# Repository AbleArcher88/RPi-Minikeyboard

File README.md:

# RPi-Minikeyboard
Handheld minerature keyboard for Raspberry Pi 4 (and hopefully later)

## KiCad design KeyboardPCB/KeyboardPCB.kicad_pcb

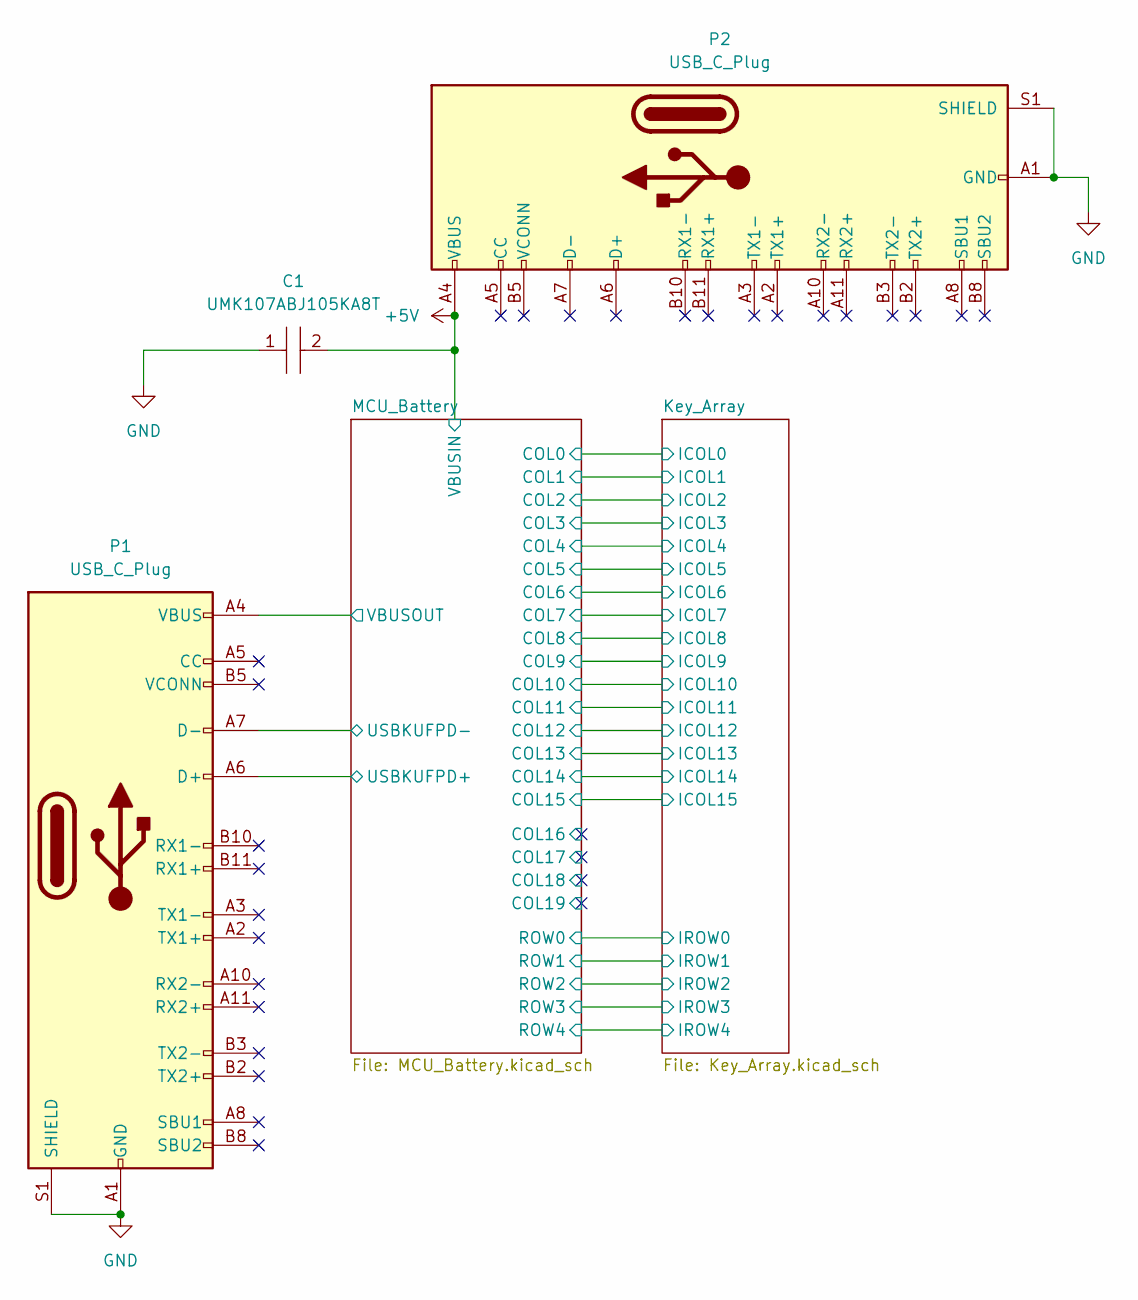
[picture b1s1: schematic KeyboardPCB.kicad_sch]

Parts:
C1: UMK107ABJ105KA8T; CAPC1608X95N; Mouser Part Number 963-UMK107ABJ105KA8T
P1, P2: USB_C_Plug; USB_C_Receptacle_Amphenol_12401548E4-2A

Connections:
+5V: C1.2, P2.A4 (VBUS), P2.A9 (VBUS), P2.B4 (VBUS), P2.B9 (VBUS); also elsewhere on the board
/MCU_Battery/USBKUFPD+: P1.A6 (D+); also elsewhere on the board
/MCU_Battery/USBKUFPD-: P1.A7 (D-); also elsewhere on the board
/MCU_Battery/VBUSOUT: P1.A4 (VBUS), P1.A9 (VBUS), P1.B4 (VBUS), P1.B9 (VBUS); also elsewhere on the board
GND: C1.1, P1.A1 (GND), P1.A12 (GND), P1.B1 (GND), P1.B12 (GND), P1.S1 (SHIELD), P2.A1 (GND), P2.A12 (GND), P2.B1 (GND), P2.B12 (GND), P2.S1 (SHIELD); also elsewhere on the board

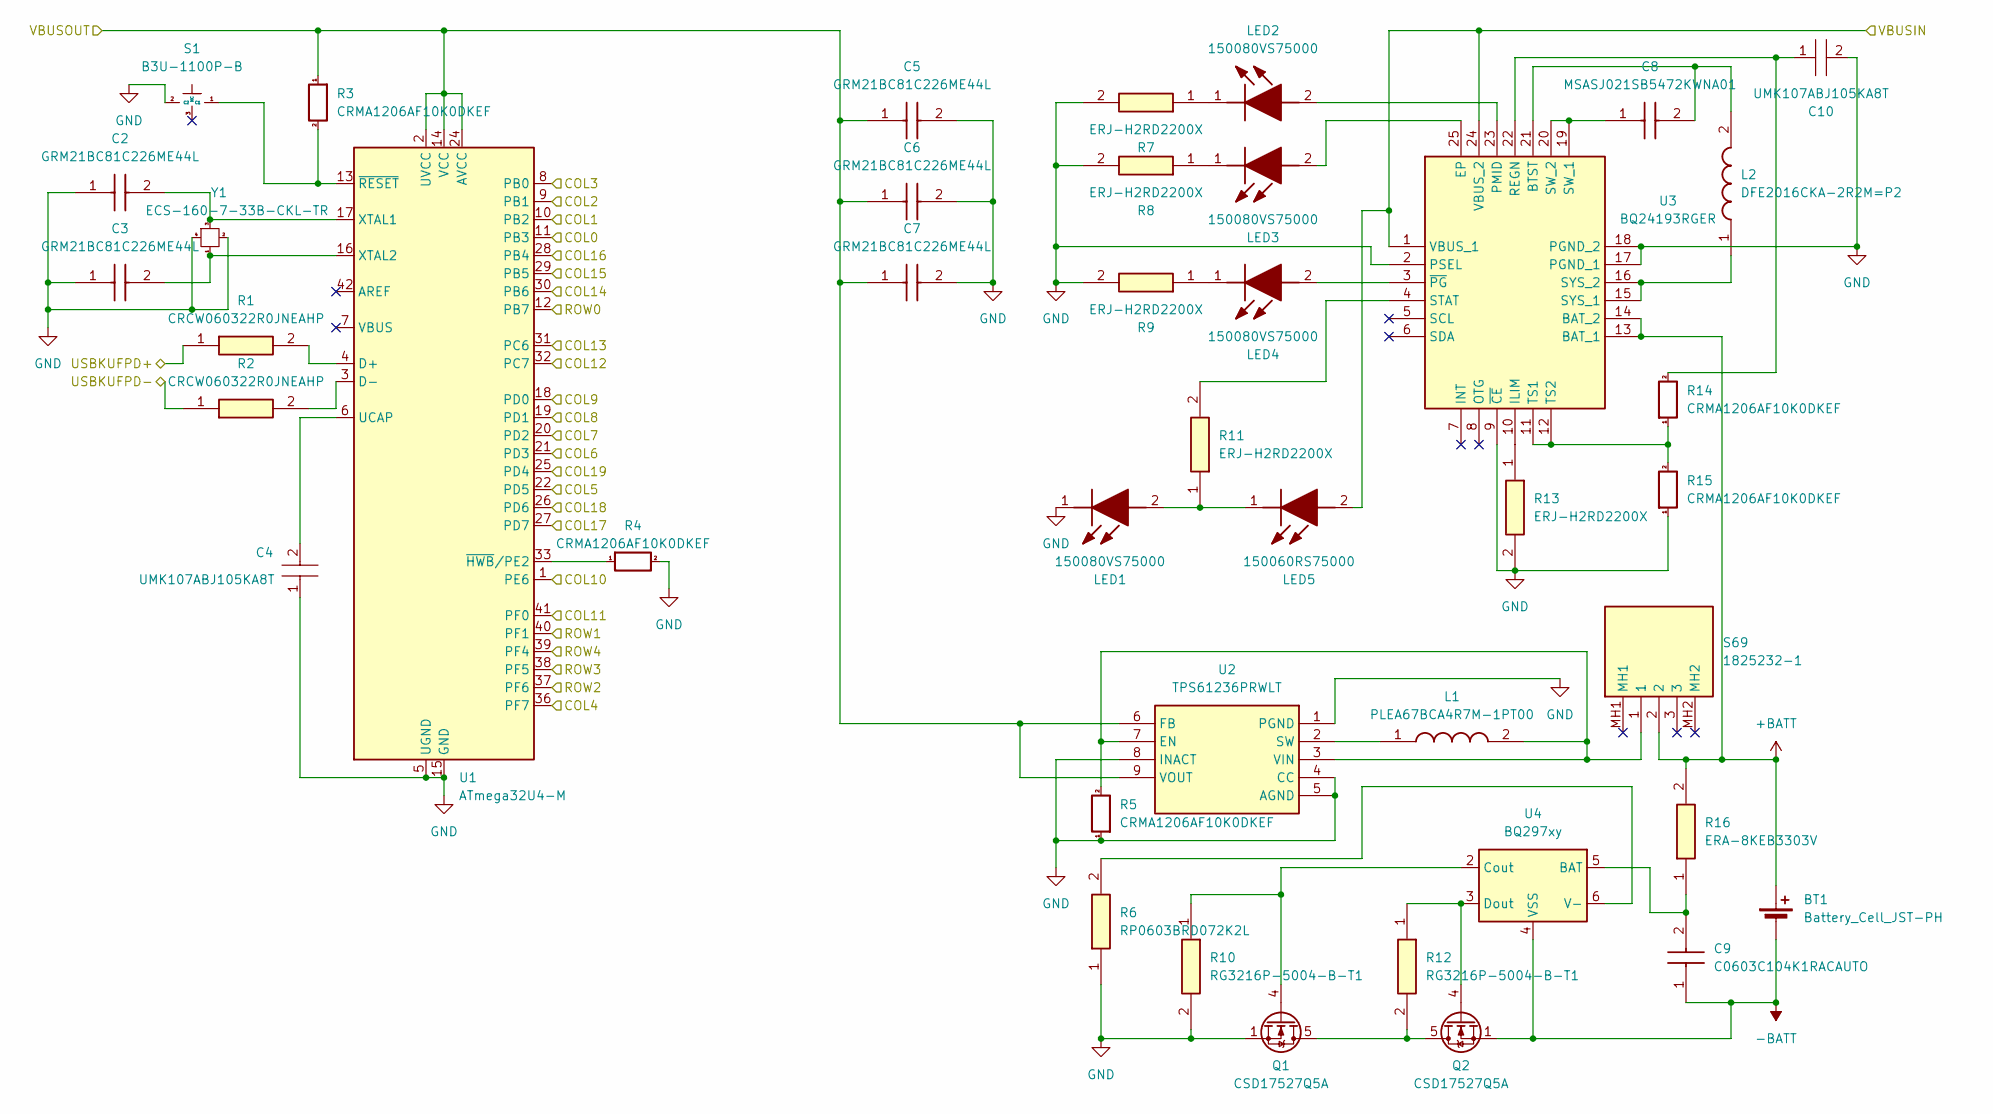
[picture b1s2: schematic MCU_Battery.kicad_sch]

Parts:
BT1: Battery_Cell_JST-PH; JST_PH_B2B-PH-K_1x02_P2.00mm_Vertical
C2, C3, C5, C6, C7: GRM21BC81C226ME44L; CAPC2012X145N; Manufacturer_Part_Number GRM21BC81C226ME44L; Mouser Part Number 81-GRM21BC81C226ME4L
C4, C10: UMK107ABJ105KA8T; CAPC1608X95N; Mouser Part Number 963-UMK107ABJ105KA8T
C8: MSASJ021SB5472KWNA01; CAPC0201X14N; Manufacturer_Part_Number MSASJ021SB5472KWNA01; Mouser Part Number 963-MSASJ021SB5472KW
C9: C0603C104K1RACAUTO; CAPC1608X95N; Manufacturer_Part_Number C0603C104K1RACAUTO; Mouser Part Number 80-C0603C104K1RAUTO
L1: PLEA67BCA4R7M-1PT00; PLEA67BCA4R7M1PT00; Manufacturer_Part_Number PLEA67BCA4R7M-1PT00; Mouser Part Number 810-PLEA67BCA4R7M1PT
L2: DFE2016CKA-2R2M=P2; DFE2016CKA1R0MP2; Manufacturer_Part_Number DFE2016CKA-2R2M=P2; Mouser Part Number 81-DFE2016CKA2R2M=P2
LED1, LED2, LED3, LED4: 150080VS75000; LEDC2012X80N; Manufacturer_Part_Number 150080VS75000; Mouser Part Number 710-150080VS75000
LED5: 150060RS75000; LEDC1608X80N; Manufacturer_Part_Number 150060RS75000; Mouser Part Number 710-150060RS75000
Q1, Q2: CSD17527Q5A; TDSON-8-1
R1, R2: CRCW060322R0JNEAHP; RESC1608X50N; Manufacturer_Part_Number CRCW060322R0JNEAHP; Mouser Part Number 71-CRCW060322R0JNEAH
R3, R4, R5, R14, R15: CRMA1206AF10K0DKEF; RESC3216X74N; Mouser Part Number 71-CRMA1206AF10K0DKF
R6: RP0603BRD072K2L; RESC1608X55N; Manufacturer_Part_Number RP0603BRD072K2L; Mouser Part Number 603-RP0603BRD072K2L
R7, R8, R9, R11, R13: ERJ-H2RD2200X; H2C_H2R; Manufacturer_Part_Number ERJ-H2RD2200X; Mouser Part Number 667-ERJ-H2RD2200X
R10, R12: RG3216P-5004-B-T1; RESC3216X50N; Manufacturer_Part_Number RG3216P-5004-B-T1; Mouser Part Number 754-RG3216P-5004B-T1
R16: ERA-8KEB3303V; ERA8KEB1004V; Manufacturer_Part_Number ERA-8KEB3303V; Mouser Part Number 667-ERA-8KEB3303V
S1: B3U-1100P-B; B3U1100PB; Manufacturer_Part_Number B3U-1100P-B; Mouser Part Number 653-B3U-1100P-B
S69: 1825232-1; 18252321; Manufacturer_Part_Number 1825232-1; Mouser Part Number 655-1825232-1
U1: ATmega32U4-M; QFN-44-1EP_7x7mm_P0.5mm_EP5.2x5.2mm
U2: TPS61236PRWLT; TPS61235PRWLT; Manufacturer_Part_Number TPS61236PRWLT; Mouser Part Number 595-TPS61236PRWLT
U3: BQ24193RGER; QFN50P400X400X100-25N-D; Manufacturer_Part_Number BQ24193RGER; Mouser Part Number 595-BQ24193RGER
U4: BQ297xy; WSON-6_1.5x1.5mm_P0.5mm
Y1: ECS-160-7-33B-CKL-TR; ECS160733BCKLTR; Manufacturer_Part_Number ECS-160-7-33B-CKL-TR

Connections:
+5V: LED5.2 (A), U3.1 (VBUS_1), U3.24 (VBUS_2); also elsewhere on the board
+BATT: BT1.1 (+), R16.2, S69.2, U3.13 (BAT_1), U3.14 (BAT_2)
-BATT: BT1.2 (-), C9.1, Q2.1 (S), Q2.2 (S), Q2.3 (S), U4.4 (VSS)
/Key_Array/ICOL0: U1.11 (PB3); also elsewhere on the board
/Key_Array/ICOL1: U1.10 (PB2); also elsewhere on the board
/Key_Array/ICOL2: U1.9 (PB1); also elsewhere on the board
/Key_Array/ICOL3: U1.8 (PB0); also elsewhere on the board
/Key_Array/ICOL4: U1.36 (PF7); also elsewhere on the board
/Key_Array/ICOL5: U1.22 (PD5); also elsewhere on the board
/Key_Array/ICOL6: U1.21 (PD3); also elsewhere on the board
/Key_Array/ICOL7: U1.20 (PD2); also elsewhere on the board
/Key_Array/ICOL8: U1.19 (PD1); also elsewhere on the board
/Key_Array/ICOL9: U1.18 (PD0); also elsewhere on the board
/Key_Array/ICOL10: U1.1 (PE6); also elsewhere on the board
/Key_Array/ICOL11: U1.41 (PF0); also elsewhere on the board
/Key_Array/ICOL12: U1.32 (PC7); also elsewhere on the board
/Key_Array/ICOL13: U1.31 (PC6); also elsewhere on the board
/Key_Array/ICOL14: U1.30 (PB6)
/Key_Array/ICOL15: U1.29 (PB5)
/Key_Array/IROW0: U1.12 (PB7); also elsewhere on the board
/Key_Array/IROW1: U1.40 (PF1); also elsewhere on the board
/Key_Array/IROW2: U1.37 (PF6); also elsewhere on the board
/Key_Array/IROW3: U1.38 (PF5); also elsewhere on the board
/Key_Array/IROW4: U1.39 (PF4); also elsewhere on the board
/MCU_Battery/COL16: U1.28 (PB4)
/MCU_Battery/COL17: U1.27 (PD7)
/MCU_Battery/COL18: U1.26 (PD6)
/MCU_Battery/COL19: U1.25 (PD4)
/MCU_Battery/USBKUFPD+: R1.1; also elsewhere on the board
/MCU_Battery/USBKUFPD-: R2.1; also elsewhere on the board
/MCU_Battery/VBUSOUT: C5.1, C6.1, C7.1, R3.1, U1.2 (UVCC), U1.14 (VCC), U1.24 (AVCC), U1.34 (VCC), U1.44 (AVCC), U2.6 (FB), U2.9 (VOUT); also elsewhere on the board
GND: C2.1, C3.1, C4.1, C5.2, C6.2, C7.2, C10.2, LED1.1 (K), Q1.1 (S), Q1.2 (S), Q1.3 (S), R4.2, R5.1, R6.1, R7.2, R8.2, R9.2, R10.2, R13.2, R15.1, S1.2 (C2), U1.5 (UGND), U1.15 (GND), U1.23 (GND), U1.35 (GND), U1.43 (GND), U1.45 (GND), U2.1 (PGND), U2.4 (CC), U2.5 (AGND), U2.8 (INACT), U3.2 (PSEL), U3.9 (~CE), U3.17 (PGND_1), U3.18 (PGND_2), Y1.2, Y1.4; also elsewhere on the board
unnamed: LED1.2 (A), LED5.1 (K), R11.1
unnamed: LED2.2 (A), U3.23 (PMID)
unnamed: LED2.1 (K), R7.1
unnamed: LED3.2 (A), U3.25 (EP)
unnamed: LED3.1 (K), R8.1
unnamed: LED4.2 (A), U3.3 (~PG)
unnamed: LED4.1 (K), R9.1
unnamed: Q1.5 (D), Q2.5 (D), R12.2
unnamed: Q1.4 (G), R10.1, U4.2 (Cout)
unnamed: Q2.4 (G), R12.1, U4.3 (Dout)
unnamed: R3.2, S1.1 (C1), U1.13 (~RESET)
unnamed: R1.2, U1.4 (D+)
unnamed: R2.2, U1.3 (D-)
unnamed: C4.2, U1.6 (UCAP)
unnamed: C2.2, U1.17 (XTAL1), Y1.3
unnamed: C3.2, U1.16 (XTAL2), Y1.1
unnamed: R4.1, U1.33 (~HWB/PE2)
unnamed: L1.2, R5.2, S69.1, U2.3 (VIN), U2.7 (EN)
unnamed: L1.1, U2.2 (SW)
unnamed: C8.2, L2.2, U3.21 (BTST)
unnamed: R13.1, U3.10 (ILIM)
unnamed: C10.1, R14.2, U3.22 (REGN)
unnamed: R11.2, U3.4 (STAT)
unnamed: C8.1, U3.19 (SW_1), U3.20 (SW_2)
unnamed: L2.1, U3.15 (SYS_1), U3.16 (SYS_2)
unnamed: R14.1, R15.2, U3.11 (TS1), U3.12 (TS2)
unnamed: C9.2, R16.1, U4.5 (BAT)
unnamed: R6.2, U4.6 (V-)

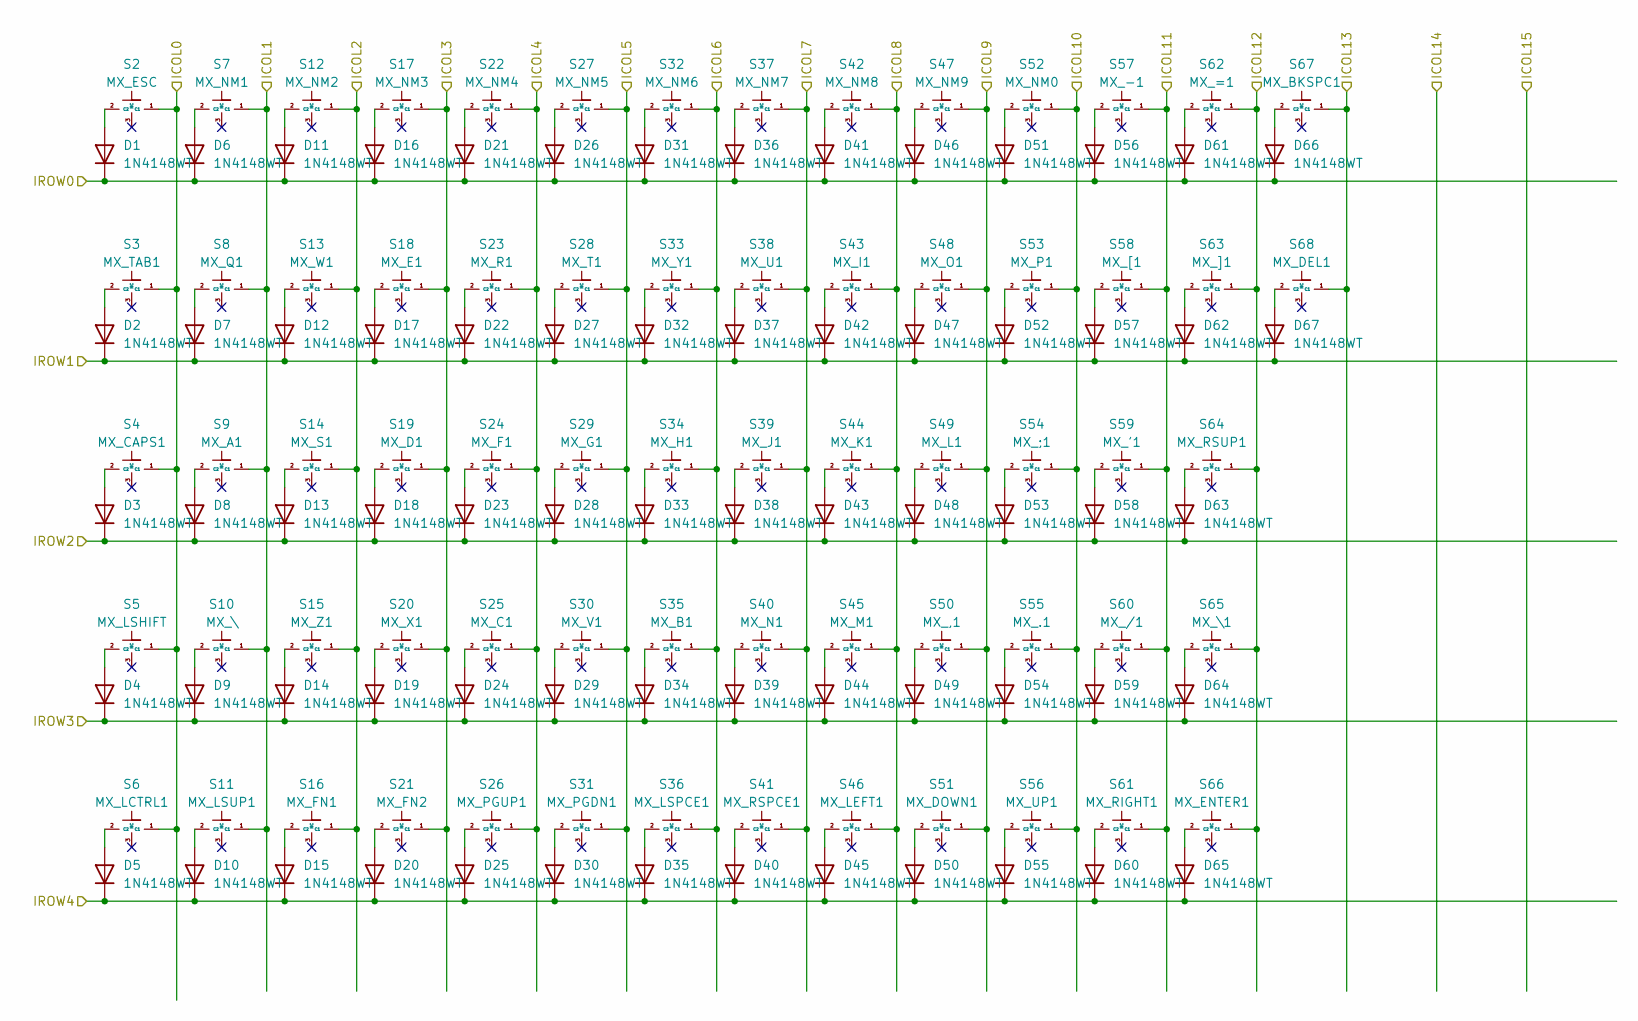
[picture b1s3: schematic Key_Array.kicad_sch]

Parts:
D1, D2, D3, D4, D5, D6, D7, D8, D9, D10, D11, D12, D13, D14, D15, D16, D17, D18, D19, D20, D21, D22, D23, D24, D25, D26, D27, D28, D29, D30, D31, D32, D33, D34, D35, D36, D37, D38, D39, D40, D41, D42, D43, D44, D45, D46, D47, D48, D49, D50, D51, D52, D53, D54, D55, D56, D57, D58, D59, D60, D61, D62, D63, D64, D65, D66, D67: 1N4148WT; D_SOD-523
S2: MX_ESC; B3U1100PB; Manufacturer_Part_Number B3U-1100P-B; Mouser Part Number 653-B3U-1100P-B
S3: MX_TAB1; B3U1100PB; Manufacturer_Part_Number B3U-1100P-B; Mouser Part Number 653-B3U-1100P-B
S4: MX_CAPS1; B3U1100PB; Manufacturer_Part_Number B3U-1100P-B; Mouser Part Number 653-B3U-1100P-B
S5: MX_LSHIFT; B3U1100PB; Manufacturer_Part_Number B3U-1100P-B; Mouser Part Number 653-B3U-1100P-B
S6: MX_LCTRL1; B3U1100PB; Manufacturer_Part_Number B3U-1100P-B; Mouser Part Number 653-B3U-1100P-B
S7: MX_NM1; B3U1100PB; Manufacturer_Part_Number B3U-1100P-B; Mouser Part Number 653-B3U-1100P-B
S8: MX_Q1; B3U1100PB; Manufacturer_Part_Number B3U-1100P-B; Mouser Part Number 653-B3U-1100P-B
S9: MX_A1; B3U1100PB; Manufacturer_Part_Number B3U-1100P-B; Mouser Part Number 653-B3U-1100P-B
S10: MX_\; B3U1100PB; Manufacturer_Part_Number B3U-1100P-B; Mouser Part Number 653-B3U-1100P-B
S11: MX_LSUP1; B3U1100PB; Manufacturer_Part_Number B3U-1100P-B; Mouser Part Number 653-B3U-1100P-B
S12: MX_NM2; B3U1100PB; Manufacturer_Part_Number B3U-1100P-B; Mouser Part Number 653-B3U-1100P-B
S13: MX_W1; B3U1100PB; Manufacturer_Part_Number B3U-1100P-B; Mouser Part Number 653-B3U-1100P-B
S14: MX_S1; B3U1100PB; Manufacturer_Part_Number B3U-1100P-B; Mouser Part Number 653-B3U-1100P-B
S15: MX_Z1; B3U1100PB; Manufacturer_Part_Number B3U-1100P-B; Mouser Part Number 653-B3U-1100P-B
S16: MX_FN1; B3U1100PB; Manufacturer_Part_Number B3U-1100P-B; Mouser Part Number 653-B3U-1100P-B
S17: MX_NM3; B3U1100PB; Manufacturer_Part_Number B3U-1100P-B; Mouser Part Number 653-B3U-1100P-B
S18: MX_E1; B3U1100PB; Manufacturer_Part_Number B3U-1100P-B; Mouser Part Number 653-B3U-1100P-B
S19: MX_D1; B3U1100PB; Manufacturer_Part_Number B3U-1100P-B; Mouser Part Number 653-B3U-1100P-B
S20: MX_X1; B3U1100PB; Manufacturer_Part_Number B3U-1100P-B; Mouser Part Number 653-B3U-1100P-B
S21: MX_FN2; B3U1100PB; Manufacturer_Part_Number B3U-1100P-B; Mouser Part Number 653-B3U-1100P-B
S22: MX_NM4; B3U1100PB; Manufacturer_Part_Number B3U-1100P-B; Mouser Part Number 653-B3U-1100P-B
S23: MX_R1; B3U1100PB; Manufacturer_Part_Number B3U-1100P-B; Mouser Part Number 653-B3U-1100P-B
S24: MX_F1; B3U1100PB; Manufacturer_Part_Number B3U-1100P-B; Mouser Part Number 653-B3U-1100P-B
S25: MX_C1; B3U1100PB; Manufacturer_Part_Number B3U-1100P-B; Mouser Part Number 653-B3U-1100P-B
S26: MX_PGUP1; B3U1100PB; Manufacturer_Part_Number B3U-1100P-B; Mouser Part Number 653-B3U-1100P-B
S27: MX_NM5; B3U1100PB; Manufacturer_Part_Number B3U-1100P-B; Mouser Part Number 653-B3U-1100P-B
S28: MX_T1; B3U1100PB; Manufacturer_Part_Number B3U-1100P-B; Mouser Part Number 653-B3U-1100P-B
S29: MX_G1; B3U1100PB; Manufacturer_Part_Number B3U-1100P-B; Mouser Part Number 653-B3U-1100P-B
S30: MX_V1; B3U1100PB; Manufacturer_Part_Number B3U-1100P-B; Mouser Part Number 653-B3U-1100P-B
S31: MX_PGDN1; B3U1100PB; Manufacturer_Part_Number B3U-1100P-B; Mouser Part Number 653-B3U-1100P-B
S32: MX_NM6; B3U1100PB; Manufacturer_Part_Number B3U-1100P-B; Mouser Part Number 653-B3U-1100P-B
S33: MX_Y1; B3U1100PB; Manufacturer_Part_Number B3U-1100P-B; Mouser Part Number 653-B3U-1100P-B
S34: MX_H1; B3U1100PB; Manufacturer_Part_Number B3U-1100P-B; Mouser Part Number 653-B3U-1100P-B
S35: MX_B1; B3U1100PB; Manufacturer_Part_Number B3U-1100P-B; Mouser Part Number 653-B3U-1100P-B
S36: MX_LSPCE1; B3U1100PB; Manufacturer_Part_Number B3U-1100P-B; Mouser Part Number 653-B3U-1100P-B
S37: MX_NM7; B3U1100PB; Manufacturer_Part_Number B3U-1100P-B; Mouser Part Number 653-B3U-1100P-B
S38: MX_U1; B3U1100PB; Manufacturer_Part_Number B3U-1100P-B; Mouser Part Number 653-B3U-1100P-B
S39: MX_J1; B3U1100PB; Manufacturer_Part_Number B3U-1100P-B; Mouser Part Number 653-B3U-1100P-B
S40: MX_N1; B3U1100PB; Manufacturer_Part_Number B3U-1100P-B; Mouser Part Number 653-B3U-1100P-B
S41: MX_RSPCE1; B3U1100PB; Manufacturer_Part_Number B3U-1100P-B; Mouser Part Number 653-B3U-1100P-B
S42: MX_NM8; B3U1100PB; Manufacturer_Part_Number B3U-1100P-B; Mouser Part Number 653-B3U-1100P-B
S43: MX_I1; B3U1100PB; Manufacturer_Part_Number B3U-1100P-B; Mouser Part Number 653-B3U-1100P-B
S44: MX_K1; B3U1100PB; Manufacturer_Part_Number B3U-1100P-B; Mouser Part Number 653-B3U-1100P-B
S45: MX_M1; B3U1100PB; Manufacturer_Part_Number B3U-1100P-B; Mouser Part Number 653-B3U-1100P-B
S46: MX_LEFT1; B3U1100PB; Manufacturer_Part_Number B3U-1100P-B; Mouser Part Number 653-B3U-1100P-B
S47: MX_NM9; B3U1100PB; Manufacturer_Part_Number B3U-1100P-B; Mouser Part Number 653-B3U-1100P-B
S48: MX_O1; B3U1100PB; Manufacturer_Part_Number B3U-1100P-B; Mouser Part Number 653-B3U-1100P-B
S49: MX_L1; B3U1100PB; Manufacturer_Part_Number B3U-1100P-B; Mouser Part Number 653-B3U-1100P-B
S50: MX_,1; B3U1100PB; Manufacturer_Part_Number B3U-1100P-B; Mouser Part Number 653-B3U-1100P-B
S51: MX_DOWN1; B3U1100PB; Manufacturer_Part_Number B3U-1100P-B; Mouser Part Number 653-B3U-1100P-B
S52: MX_NM0; B3U1100PB; Manufacturer_Part_Number B3U-1100P-B; Mouser Part Number 653-B3U-1100P-B
S53: MX_P1; B3U1100PB; Manufacturer_Part_Number B3U-1100P-B; Mouser Part Number 653-B3U-1100P-B
S54: MX_;1; B3U1100PB; Manufacturer_Part_Number B3U-1100P-B; Mouser Part Number 653-B3U-1100P-B
S55: MX_.1; B3U1100PB; Manufacturer_Part_Number B3U-1100P-B; Mouser Part Number 653-B3U-1100P-B
S56: MX_UP1; B3U1100PB; Manufacturer_Part_Number B3U-1100P-B; Mouser Part Number 653-B3U-1100P-B
S57: MX_-1; B3U1100PB; Manufacturer_Part_Number B3U-1100P-B; Mouser Part Number 653-B3U-1100P-B
S58: MX_[1; B3U1100PB; Manufacturer_Part_Number B3U-1100P-B; Mouser Part Number 653-B3U-1100P-B
S59: MX_'1; B3U1100PB; Manufacturer_Part_Number B3U-1100P-B; Mouser Part Number 653-B3U-1100P-B
S60: MX_/1; B3U1100PB; Manufacturer_Part_Number B3U-1100P-B; Mouser Part Number 653-B3U-1100P-B
S61: MX_RIGHT1; B3U1100PB; Manufacturer_Part_Number B3U-1100P-B; Mouser Part Number 653-B3U-1100P-B
S62: MX_=1; B3U1100PB; Manufacturer_Part_Number B3U-1100P-B; Mouser Part Number 653-B3U-1100P-B
S63: MX_]1; B3U1100PB; Manufacturer_Part_Number B3U-1100P-B; Mouser Part Number 653-B3U-1100P-B
S64: MX_RSUP1; B3U1100PB; Manufacturer_Part_Number B3U-1100P-B; Mouser Part Number 653-B3U-1100P-B
S65: MX_\1; B3U1100PB; Manufacturer_Part_Number B3U-1100P-B; Mouser Part Number 653-B3U-1100P-B
S66: MX_ENTER1; B3U1100PB; Manufacturer_Part_Number B3U-1100P-B; Mouser Part Number 653-B3U-1100P-B
S67: MX_BKSPC1; B3U1100PB; Manufacturer_Part_Number B3U-1100P-B; Mouser Part Number 653-B3U-1100P-B
S68: MX_DEL1; B3U1100PB; Manufacturer_Part_Number B3U-1100P-B; Mouser Part Number 653-B3U-1100P-B

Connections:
/Key_Array/ICOL0: S2.1 (C1), S3.1 (C1), S4.1 (C1), S5.1 (C1), S6.1 (C1); also elsewhere on the board
/Key_Array/ICOL1: S7.1 (C1), S8.1 (C1), S9.1 (C1), S10.1 (C1), S11.1 (C1); also elsewhere on the board
/Key_Array/ICOL2: S12.1 (C1), S13.1 (C1), S14.1 (C1), S15.1 (C1), S16.1 (C1); also elsewhere on the board
/Key_Array/ICOL3: S17.1 (C1), S18.1 (C1), S19.1 (C1), S20.1 (C1), S21.1 (C1); also elsewhere on the board
/Key_Array/ICOL4: S22.1 (C1), S23.1 (C1), S24.1 (C1), S25.1 (C1), S26.1 (C1); also elsewhere on the board
/Key_Array/ICOL5: S27.1 (C1), S28.1 (C1), S29.1 (C1), S30.1 (C1), S31.1 (C1); also elsewhere on the board
/Key_Array/ICOL6: S32.1 (C1), S33.1 (C1), S34.1 (C1), S35.1 (C1), S36.1 (C1); also elsewhere on the board
/Key_Array/ICOL7: S37.1 (C1), S38.1 (C1), S39.1 (C1), S40.1 (C1), S41.1 (C1); also elsewhere on the board
/Key_Array/ICOL8: S42.1 (C1), S43.1 (C1), S44.1 (C1), S45.1 (C1), S46.1 (C1); also elsewhere on the board
/Key_Array/ICOL9: S47.1 (C1), S48.1 (C1), S49.1 (C1), S50.1 (C1), S51.1 (C1); also elsewhere on the board
/Key_Array/ICOL10: S52.1 (C1), S53.1 (C1), S54.1 (C1), S55.1 (C1), S56.1 (C1); also elsewhere on the board
/Key_Array/ICOL11: S57.1 (C1), S58.1 (C1), S59.1 (C1), S60.1 (C1), S61.1 (C1); also elsewhere on the board
/Key_Array/ICOL12: S62.1 (C1), S63.1 (C1), S64.1 (C1), S65.1 (C1), S66.1 (C1); also elsewhere on the board
/Key_Array/ICOL13: S67.1 (C1), S68.1 (C1); also elsewhere on the board
/Key_Array/IROW0: D1.1 (K), D6.1 (K), D11.1 (K), D16.1 (K), D21.1 (K), D26.1 (K), D31.1 (K), D36.1 (K), D41.1 (K), D46.1 (K), D51.1 (K), D56.1 (K), D61.1 (K), D66.1 (K); also elsewhere on the board
/Key_Array/IROW1: D2.1 (K), D7.1 (K), D12.1 (K), D17.1 (K), D22.1 (K), D27.1 (K), D32.1 (K), D37.1 (K), D42.1 (K), D47.1 (K), D52.1 (K), D57.1 (K), D62.1 (K), D67.1 (K); also elsewhere on the board
/Key_Array/IROW2: D3.1 (K), D8.1 (K), D13.1 (K), D18.1 (K), D23.1 (K), D28.1 (K), D33.1 (K), D38.1 (K), D43.1 (K), D48.1 (K), D53.1 (K), D58.1 (K), D63.1 (K); also elsewhere on the board
/Key_Array/IROW3: D4.1 (K), D9.1 (K), D14.1 (K), D19.1 (K), D24.1 (K), D29.1 (K), D34.1 (K), D39.1 (K), D44.1 (K), D49.1 (K), D54.1 (K), D59.1 (K), D64.1 (K); also elsewhere on the board
/Key_Array/IROW4: D5.1 (K), D10.1 (K), D15.1 (K), D20.1 (K), D25.1 (K), D30.1 (K), D35.1 (K), D40.1 (K), D45.1 (K), D50.1 (K), D55.1 (K), D60.1 (K), D65.1 (K); also elsewhere on the board
unnamed: D1.2 (A), S2.2 (C2)
unnamed: D2.2 (A), S3.2 (C2)
unnamed: D3.2 (A), S4.2 (C2)
unnamed: D4.2 (A), S5.2 (C2)
unnamed: D5.2 (A), S6.2 (C2)
unnamed: D6.2 (A), S7.2 (C2)
unnamed: D7.2 (A), S8.2 (C2)
unnamed: D8.2 (A), S9.2 (C2)
unnamed: D9.2 (A), S10.2 (C2)
unnamed: D10.2 (A), S11.2 (C2)
unnamed: D11.2 (A), S12.2 (C2)
unnamed: D12.2 (A), S13.2 (C2)
unnamed: D13.2 (A), S14.2 (C2)
unnamed: D14.2 (A), S15.2 (C2)
unnamed: D15.2 (A), S16.2 (C2)
unnamed: D16.2 (A), S17.2 (C2)
unnamed: D17.2 (A), S18.2 (C2)
unnamed: D18.2 (A), S19.2 (C2)
unnamed: D19.2 (A), S20.2 (C2)
unnamed: D20.2 (A), S21.2 (C2)
unnamed: D21.2 (A), S22.2 (C2)
unnamed: D22.2 (A), S23.2 (C2)
unnamed: D23.2 (A), S24.2 (C2)
unnamed: D24.2 (A), S25.2 (C2)
unnamed: D25.2 (A), S26.2 (C2)
unnamed: D26.2 (A), S27.2 (C2)
unnamed: D27.2 (A), S28.2 (C2)
unnamed: D28.2 (A), S29.2 (C2)
unnamed: D29.2 (A), S30.2 (C2)
unnamed: D30.2 (A), S31.2 (C2)
unnamed: D31.2 (A), S32.2 (C2)
unnamed: D32.2 (A), S33.2 (C2)
unnamed: D33.2 (A), S34.2 (C2)
unnamed: D34.2 (A), S35.2 (C2)
unnamed: D35.2 (A), S36.2 (C2)
unnamed: D36.2 (A), S37.2 (C2)
unnamed: D37.2 (A), S38.2 (C2)
unnamed: D38.2 (A), S39.2 (C2)
unnamed: D39.2 (A), S40.2 (C2)
unnamed: D40.2 (A), S41.2 (C2)
unnamed: D41.2 (A), S42.2 (C2)
unnamed: D42.2 (A), S43.2 (C2)
unnamed: D43.2 (A), S44.2 (C2)
unnamed: D44.2 (A), S45.2 (C2)
unnamed: D45.2 (A), S46.2 (C2)
unnamed: D46.2 (A), S47.2 (C2)
unnamed: D47.2 (A), S48.2 (C2)
unnamed: D48.2 (A), S49.2 (C2)
unnamed: D49.2 (A), S50.2 (C2)
unnamed: D50.2 (A), S51.2 (C2)
unnamed: D51.2 (A), S52.2 (C2)
unnamed: D52.2 (A), S53.2 (C2)
unnamed: D53.2 (A), S54.2 (C2)
unnamed: D54.2 (A), S55.2 (C2)
unnamed: D55.2 (A), S56.2 (C2)
unnamed: D56.2 (A), S57.2 (C2)
unnamed: D57.2 (A), S58.2 (C2)
unnamed: D58.2 (A), S59.2 (C2)
unnamed: D59.2 (A), S60.2 (C2)
unnamed: D60.2 (A), S61.2 (C2)
unnamed: D61.2 (A), S62.2 (C2)
unnamed: D62.2 (A), S63.2 (C2)
unnamed: D63.2 (A), S64.2 (C2)
unnamed: D64.2 (A), S65.2 (C2)
unnamed: D65.2 (A), S66.2 (C2)
unnamed: D66.2 (A), S67.2 (C2)
unnamed: D67.2 (A), S68.2 (C2)

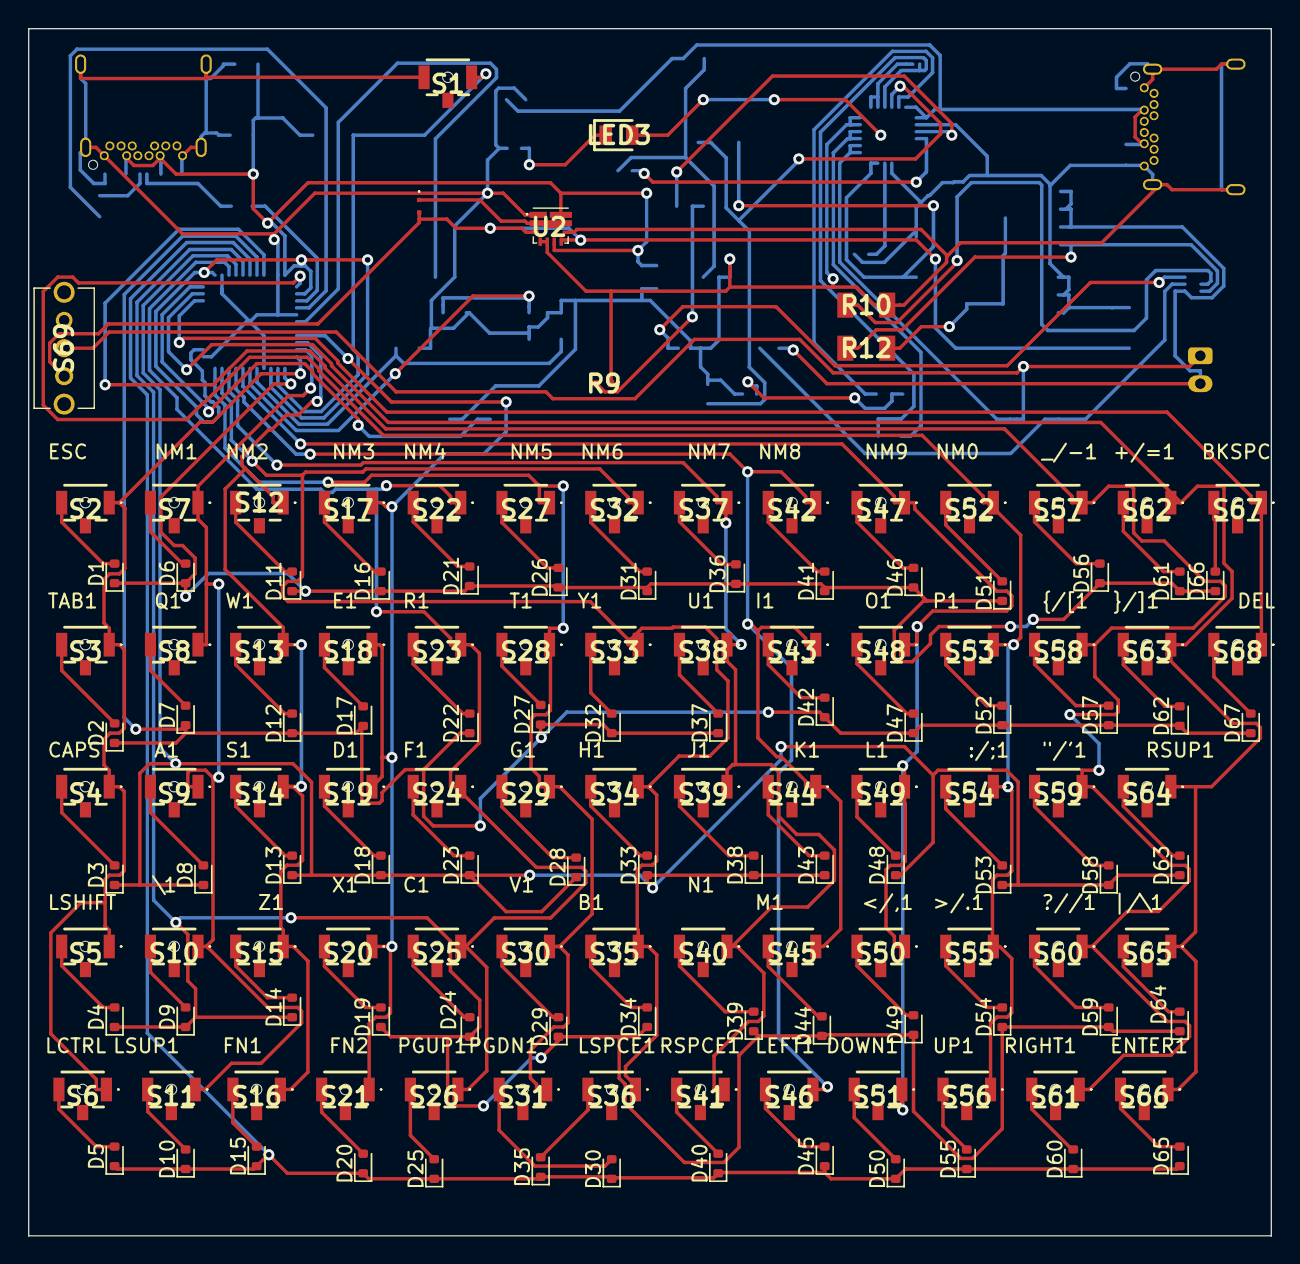
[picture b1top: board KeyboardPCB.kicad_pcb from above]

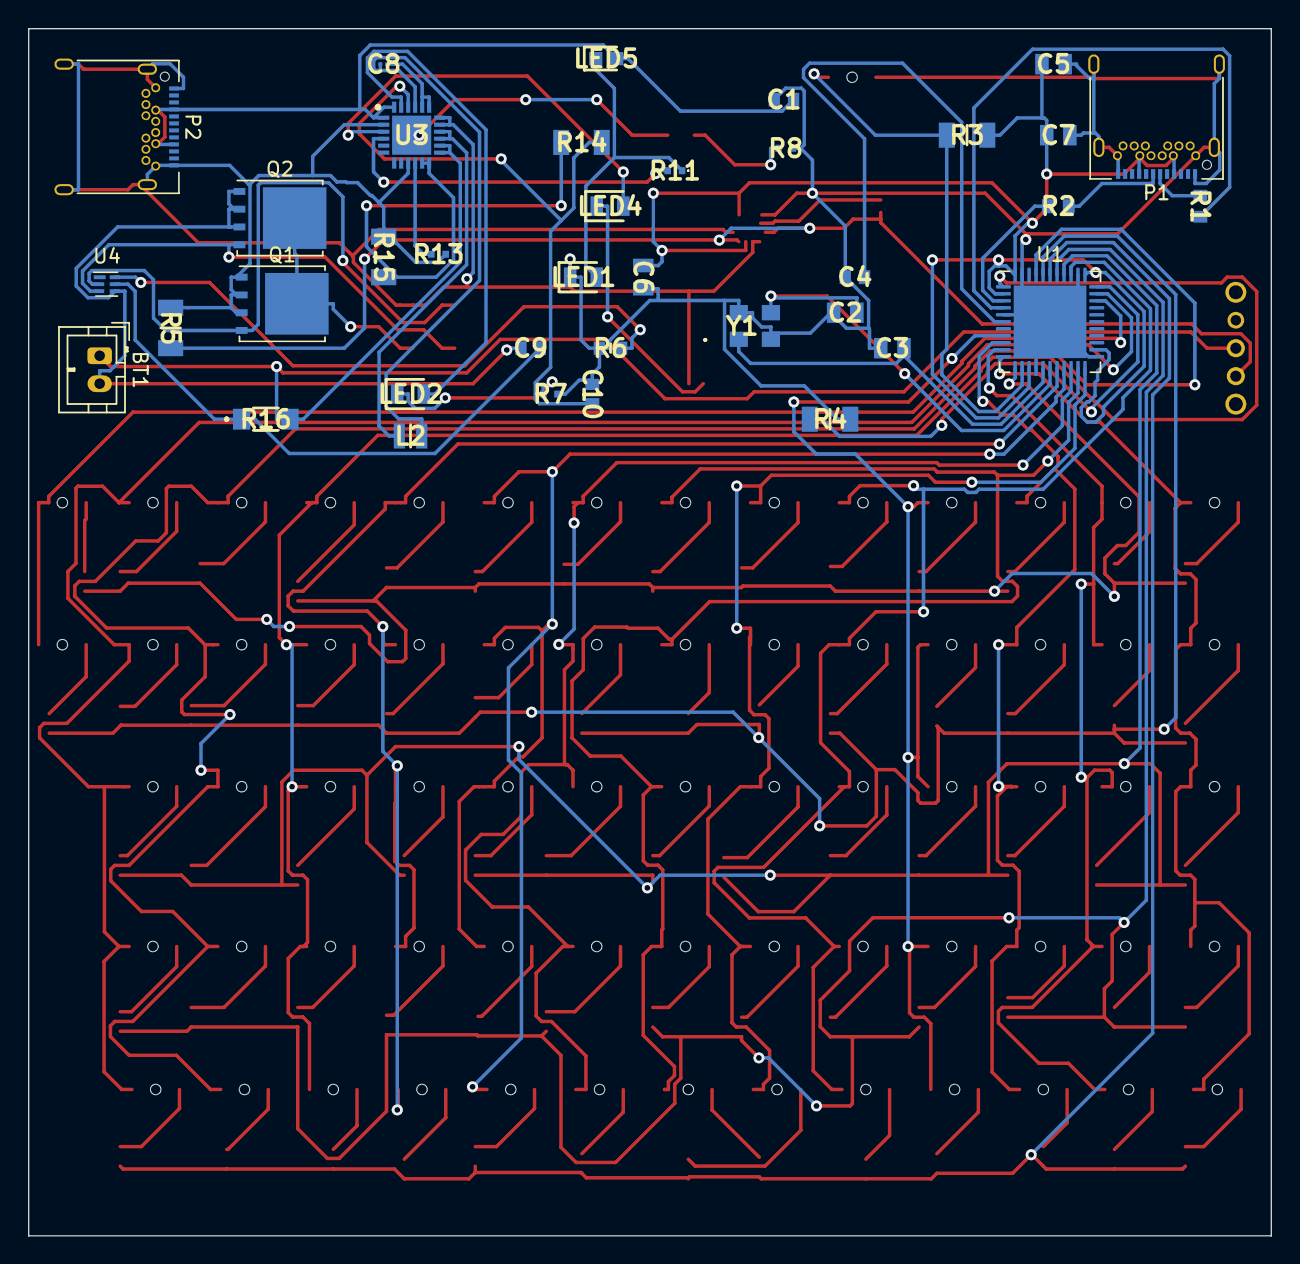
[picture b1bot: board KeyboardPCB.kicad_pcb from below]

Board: 2 copper layers, 88.9 x 86.4 mm, 179 parts (37 on the bottom side), 121 nets.

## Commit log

2023-01-05 Adding PCB files
2023-01-18 Made progress on keyboard schematic
2023-01-18 Added Sheets for main MCU/battery and key array
2023-01-18 set up for key array
2023-01-19 Worked on battery charging system
2023-02-04 keyboard added
2023-02-04 added some diodes
2023-02-04 Added a Battery Charging circuit
2023-02-04 reorganised the schematic
2023-02-04 getting rid of akwardness
2023-02-04 Equipment added
2023-02-05 Added more devices.
2023-02-05 Made progress on the key matrix, and did some part substitutions
2023-02-09 Added NCs
2023-02-11 added equipment entries
2023-02-11 added a 10k resistor
2023-04-23 Asthetic Changes
2023-04-23 Asthetic Changes #2
2023-04-23 Asthetic Modifications
2023-04-23 Symbol Modifications
2023-04-23 Reorganised key array
2023-04-23 Added some Capacitors
2023-05-20 added footprints and changed symbols
2023-05-22 Added Symbols and placed them
2023-05-23 changed several components
2023-05-24 made changes to the board
2023-09-03 Schematic Filled out
2023-09-03 populated Keyboard
2023-09-03 Began routing PCB
2023-09-03 Began work on PCB
2023-09-23 Changed switch and revised PCB layout?
2023-09-23 Finalised schematic, progress on board layout
2023-09-26 Reorganised backside
2023-10-07 "Finished" board layout
2023-10-07 Added pdf versions of drawings for ease of documentation
2023-10-07 Added pdf documentation
2023-10-09 Added switch and modified pcb to account for it
2023-11-19 Changed location of switch
2023-11-19 chore: plotted schematics for ease of use
2023-11-19 Small modification to tracks
